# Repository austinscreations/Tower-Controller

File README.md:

# Tower Controller
# formerly mini-notification-tower

I've recently found good sellers for lower cost industrial towers, while I'll still 3d print my own 180 degree tower light and share files should someone want to build one, I've now designed a semi-universal controller for controlling analog 12-24v tower lights

New code can be found here: [Github](https://github.com/austinscreations/OXRS-AC-TowerController-ESP8266-FW) <br>
Load up a bin file in wifi or ethernet mode and provision the device using the admin UI: [Github](https://github.com/OXRS-IO/OXRS-IO-AdminUI-WEB-APP) <br>
Compatable with the (http://oxrs.io) system

As someone who has a home office and a workshop in the garage I wanted an easy way to have notifications whereever I am.
traditional 5 layer led notification lights are large and pricey.
I set out to make a smaller alternative solution. with 3d printing I made a 180 degree light, with the help of a 3d printed mold I was able to use epoxy resin and tints to create the lenses.

-

Red - flashing - immediate issue (such as a fire alarm or CO alarm)

Red - machine error (cnc or 3d printer)

Yellow - flashing - machine error / require attention (such as a 3d printer filament sensor or 3d print ends)

Yellow - equipement On - temperature related (3d printer active (hot end or heat bed) or soldering iron on)

Green - equipment on but idle (say 3d printer or soldering iron is on but not running a job

Blue - notifications (with the help of an I2C lcd I'm able to show messages

White - tied to my doorbell (one to my office door and front house door)

-

Version 1 used 5mm leds in a 3d printed insert - mosfets controlelr wired to 5v and arduino nano. the arduino nano was linked to an rf433 reciever for the doorbell.

Version 2 will include a PCB for a Wemos d1 mini and SMD leds, and I want to try to make a 360 degree model as well.
          
RF433 will be offloaded to a esp-01 to build a seprate gateway for my home assitant installation.

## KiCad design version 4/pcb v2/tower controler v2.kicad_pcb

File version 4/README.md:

this latest version include builtin ethernet support, POE support and runs on esp32

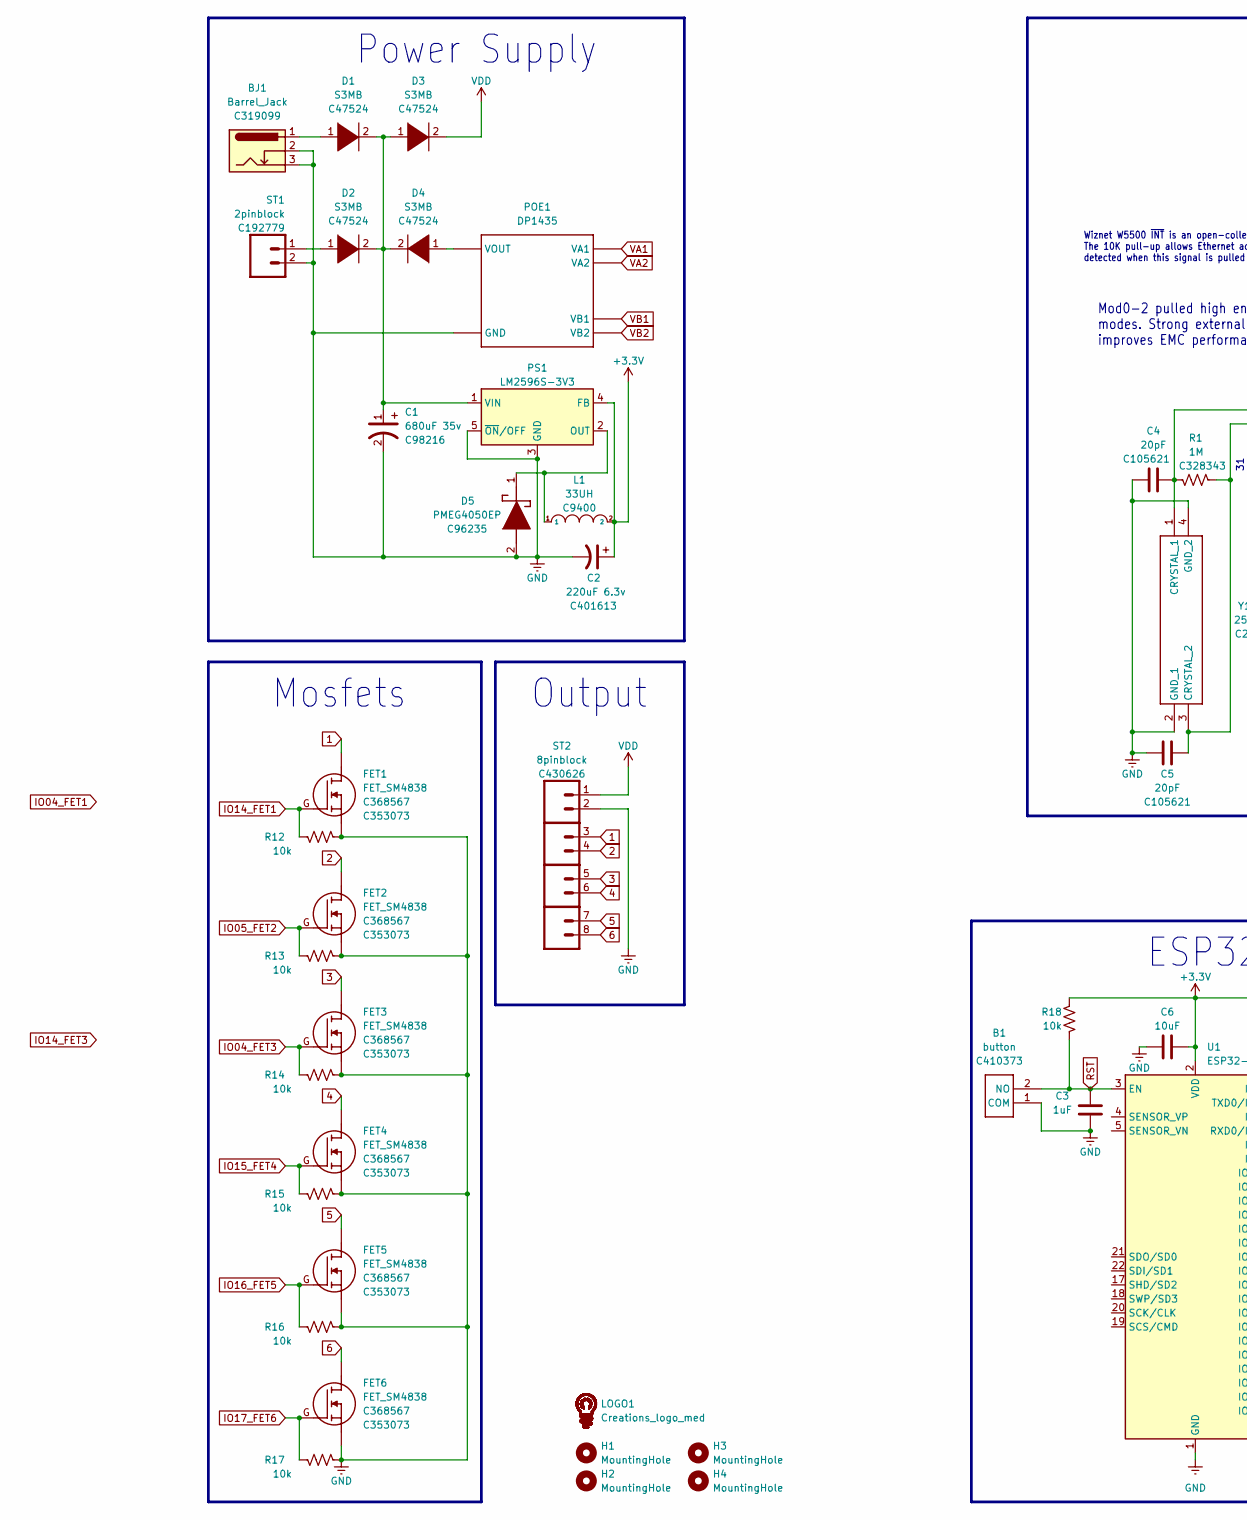
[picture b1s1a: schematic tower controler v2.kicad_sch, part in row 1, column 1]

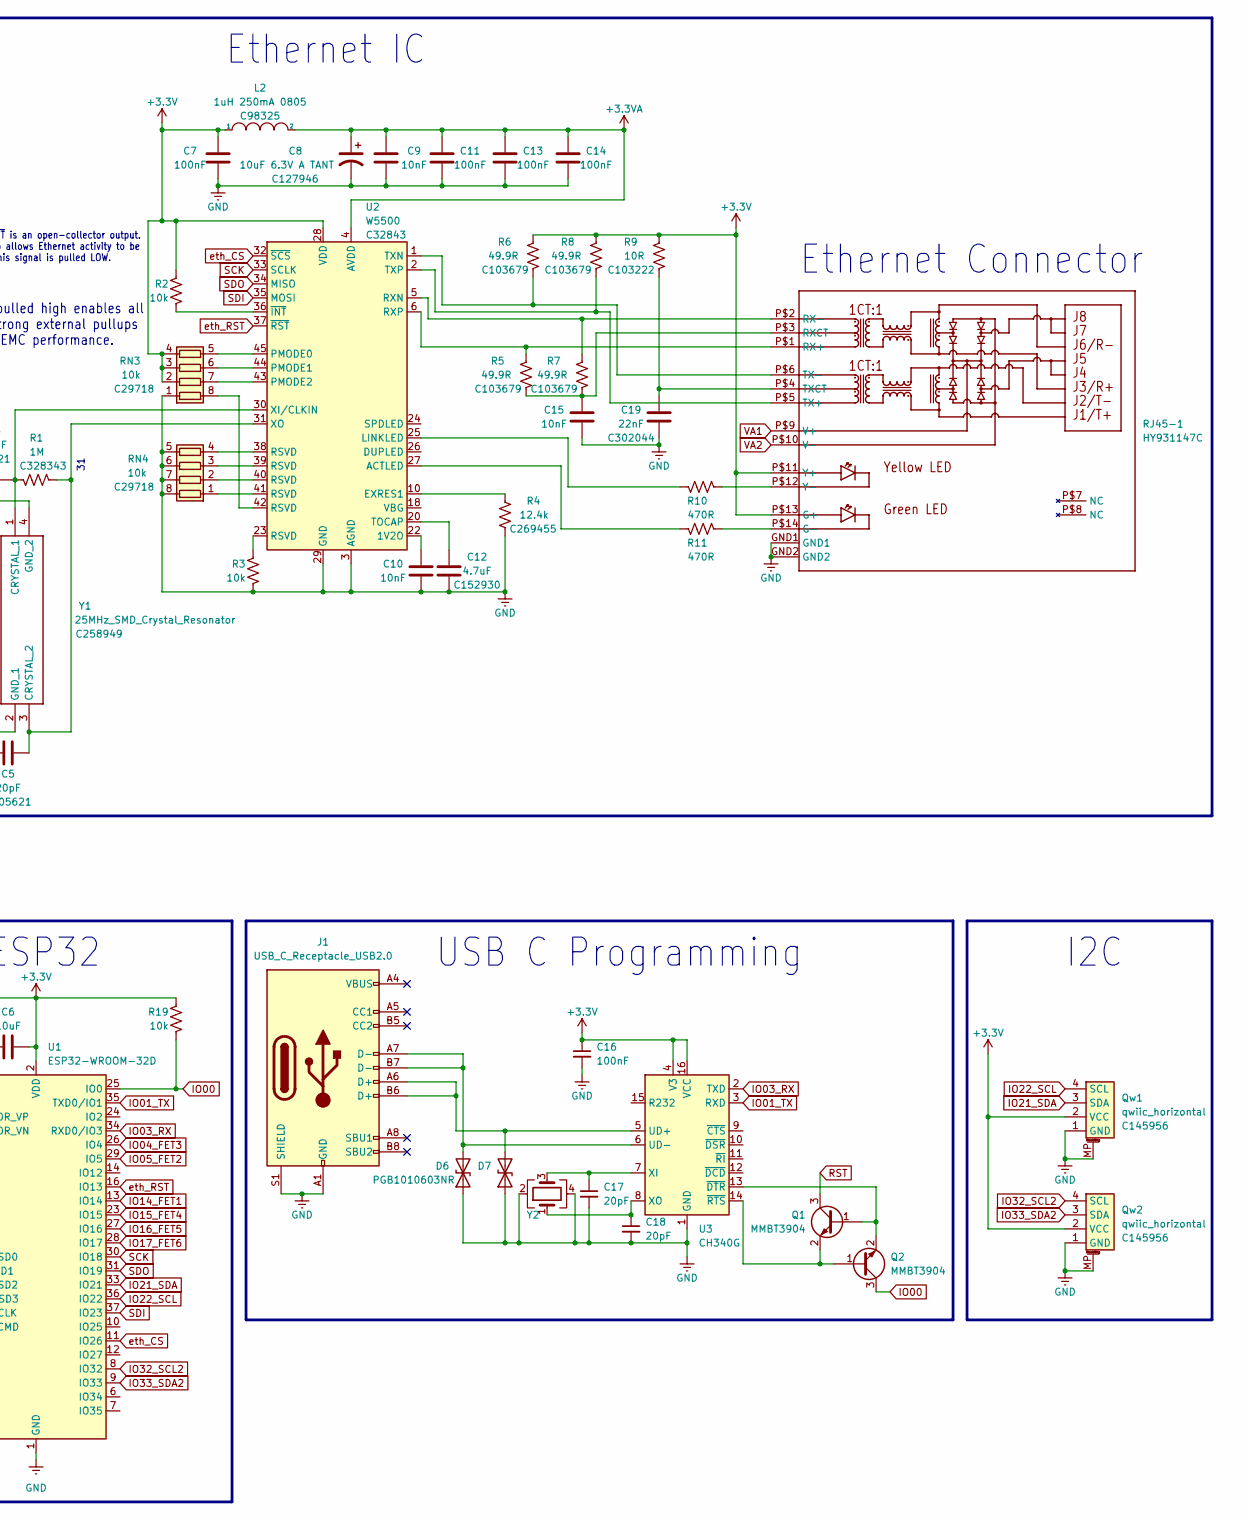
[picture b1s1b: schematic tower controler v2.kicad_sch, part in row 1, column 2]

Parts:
B1: button; part # C410373
BJ1: Barrel_Jack; Barrel Jack; part # C319099
C1: 680uF 35v; large capacitor 12.5d 13.5h; part # C98216
C2: 220uF 6.3v; CP_Elec_8x6.2; part # C401613
C3: 1uF; C_0603_1608Metric
C4, C5: 20pF; C_0603_1608Metric; part # C105621
C6: 10uF; C_0603_1608Metric
C7, C11, C13, C14, C16: 100nF; C_0603_1608Metric
C8: 10uF 6.3V A TANT; CP_EIA-3216-18_Kemet-A; part # C127946
C9, C10, C15: 10nF; C_0603_1608Metric
C12: 4.7uF; C_0603_1608Metric; part # C152930
C17, C18: 20pF; C_0603_1608Metric
C19: 22nF; C_0603_1608Metric; part # C302044
D1, D2, D3, D4: S3MB; D_SMB; part # C47524
D5: PMEG4050EP; PMEG3050EP; part # C96235
D6, D7: PGB1010603NR; D_0603_1608Metric
FET1, FET2, FET3, FET4, FET5, FET6: FET_SM4838; FET SM4838; part # C368567
H1, H2, H3, H4: MountingHole; MountingHole_3.2mm_M3
J1: USB_C_Receptacle_USB2.0; USB_C_Receptacle_HRO_TYPE-C-31-M-12
L1: 33UH; 12x12x8 inductor; part # C9400
L2: 1uH 250mA 0805; L_0805_2012Metric; part # C98325
LOGO1: Creations_logo_med; Creations logo med
POE1: DP1435
PS1: LM2596S-3V3; LM2596S
Q1, Q2: MMBT3904; SOT-23
Qw1, Qw2: qwiic_horizontal; qwiic horizontal; part # C145956
R1: 1M; R_0603_1608Metric; part # C328343
R2, R3, R12, R13, R14, R15, R16, R17, R18, R19: 10k; R_0603_1608Metric
R4: 12.4k; R_0603_1608Metric; part # C269455
R5, R6, R7, R8: 49.9R; R_0603_1608Metric; part # C103679
R9: 10R; R_0603_1608Metric; part # C103222
R10, R11: 470R; R_0603_1608Metric
RJ45-1: HY931147C
RN3, RN4: 10k; R_Array_Convex_4x0603; part # C29718
ST1: 2pinblock; part # C192779
ST2: 8pinblock; part # C430626
U1: ESP32-WROOM-32D; ESP32-WROOM-32
U2: W5500; LQFP-48_7x7mm_P0.5mm; part # C32843
U3: CH340G; SOIC-16_3.9x9.9mm_P1.27mm
Y1: 25MHz_SMD_Crystal_Resonator; part # C258949
Y2: Crystal_GND23; Crystal_SMD_3225-4Pin_3.2x2.5mm

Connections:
1: FET1.D, ST2.3
2: FET2.D, ST2.4
3: FET3.D, ST2.5
4: FET4.D, ST2.6
5: FET5.D, ST2.7
6: FET6.D, ST2.8
+3.3VA: C8.1, C9.2, C11.2, C13.2, C14.2, L2.2, U2.4 (AVDD), U2.8 (AVDD), U2.11 (AVDD), U2.15 (AVDD), U2.17 (AVDD), U2.21 (AVDD)
+3V3: C2.1, C6.2, C7.2, C16.1, L1.2, L2.1, PS1.4 (FB), Qw1.2 (VCC), Qw2.2 (VCC), R2.2, R6.2, R8.2, R9.2, R18.2, R19.2, RJ45-1.P$11 (Y+), RJ45-1.P$13 (G+), RN3.2 (R2.1), RN3.3 (R3.1), RN3.4 (R4.1), U1.2 (VDD), U2.28 (VDD), U3.4 (V3), U3.16 (VCC)
GNDREF: B1.1 (COM), BJ1.2, BJ1.3, C1.2, C2.2, C3.1, C4.1, C5.1, C6.1, C7.1, C8.2, C9.1, C10.1, C11.1, C12.1, C13.1, C14.1, C15.1, C16.2, C17.2, C18.2, C19.1, D5.2 (A), D6.1 (A1), D7.1 (A1), FET1.S, FET2.S, FET3.S, FET4.S, FET5.S, FET6.S, J1.A1 (GND), J1.A12 (GND), J1.B1 (GND), J1.B12 (GND), J1.S1 (SHIELD), POE1.GND, PS1.3 (GND), PS1.5 (~ON/OFF), Qw1.1 (GND), Qw1.MP, Qw2.1 (GND), Qw2.MP, R3.1, R4.1, R12.1, R13.1, R14.1, R15.1, R16.1, R17.1, RJ45-1.GND1, RJ45-1.GND2, RN3.1 (R1.1), RN4.5 (R4.2), RN4.6 (R3.2), RN4.7 (R2.2), RN4.8 (R1.2), ST1.2, ST2.2, U1.1 (GND), U1.15 (GND), U1.38 (GND), U1.39 (GND), U2.3 (AGND), U2.9 (AGND), U2.14 (AGND), U2.16 (AGND), U2.19 (AGND), U2.29 (GND), U2.48 (AGND), U3.1 (GND), Y1.2 (GND_1), Y1.4 (GND_2), Y2.2, Y2.4
IO00: Q2.3 (C), R19.1, U1.25 (IO0)
IO01_TX: U1.35 (TXD0/IO1), U3.3 (RXD)
IO03_RX: U1.34 (RXD0/IO3), U3.2 (TXD)
IO04_FET3: FET3.G, R14.2, U1.26 (IO4)
IO05_FET2: FET2.G, R13.2, U1.29 (IO5)
IO14_FET1: FET1.G, R12.2, U1.13 (IO14)
IO15_FET4: FET4.G, R15.2, U1.23 (IO15)
IO16_FET5: FET5.G, R16.2, U1.27 (IO16)
IO17_FET6: FET6.G, R17.2, U1.28 (IO17)
IO21_SDA: Qw1.3 (SDA), U1.33 (IO21)
IO22_SCL: Qw1.4 (SCL), U1.36 (IO22)
IO32_SCL2: Qw2.4 (SCL), U1.8 (IO32)
IO33_SDA2: Qw2.3 (SDA), U1.9 (IO33)
unnamed: BJ1.1, D1.1 (K)
unnamed: C1.1, D1.2 (A), D2.2 (A), D3.1 (K), D4.2 (A), PS1.1 (VIN)
unnamed: C4.2, R1.1, U2.30 (XI/CLKIN), Y1.1 (CRYSTAL_1)
unnamed: C5.2, R1.2, U2.31 (XO), Y1.3 (CRYSTAL_2)
unnamed: C10.2, U2.22 (1V2O)
unnamed: C12.2, U2.20 (TOCAP)
unnamed: C15.2, R5.1, R7.1, RJ45-1.P$3 (RXCT)
unnamed: C17.1, U3.7 (XI), Y2.3
unnamed: C18.1, U3.8 (XO), Y2.1
unnamed: C19.2, R9.1, RJ45-1.P$4 (TXCT)
unnamed: D2.1 (K), ST1.1
unnamed: D4.1 (K), POE1.VOUT
unnamed: D5.1 (K), L1.1, PS1.2 (OUT)
unnamed: D6.2 (A2), J1.A7 (D-), J1.B7 (D-), U3.6 (UD-)
unnamed: D7.2 (A2), J1.A6 (D+), J1.B6 (D+), U3.5 (UD+)
unnamed: Q1.1 (B), Q2.2 (E), U3.13 (~DTR)
unnamed: Q1.2 (E), Q2.1 (B), U3.14 (~RTS)
unnamed: R2.1, U2.36 (~INT)
unnamed: R3.2, U2.23 (RSVD)
unnamed: R4.2, U2.10 (EXRES1)
unnamed: R5.2, RJ45-1.P$1 (RX+), U2.6 (RXP)
unnamed: R6.1, RJ45-1.P$6 (TX-), U2.1 (TXN)
unnamed: R7.2, RJ45-1.P$2 (RX-), U2.5 (RXN)
unnamed: R8.1, RJ45-1.P$5 (TX+), U2.2 (TXP)
unnamed: R10.1, RJ45-1.P$12 (Y-)
unnamed: R10.2, U2.25 (LINKLED)
unnamed: R11.1, RJ45-1.P$14 (G-)
unnamed: R11.2, U2.27 (ACTLED)
unnamed: RN3.5 (R4.2), U2.45 (PMODE0)
unnamed: RN3.6 (R3.2), U2.44 (PMODE1)
unnamed: RN3.7 (R2.2), U2.43 (PMODE2)
unnamed: RN3.8 (R1.2), U2.42 (RSVD)
unnamed: RN4.1 (R1.1), U2.41 (RSVD)
unnamed: RN4.2 (R2.1), U2.40 (RSVD)
unnamed: RN4.3 (R3.1), U2.39 (RSVD)
unnamed: RN4.4 (R4.1), U2.38 (RSVD)
RST: B1.2 (NO), C3.2, Q1.3 (C), R18.1, U1.3 (EN)
SCK: U1.30 (IO18), U2.33 (SCLK)
SDI: U1.37 (IO23), U2.35 (MOSI)
SDO: U1.31 (IO19), U2.34 (MISO)
VA1: POE1.VA1, RJ45-1.P$9 (V+)
VA2: POE1.VA2, RJ45-1.P$10 (V-)
VB1: POE1.VB1
VB2: POE1.VB2
VDD: D3.2 (A), ST2.1
eth_CS: U1.11 (IO26), U2.32 (~SCS)
eth_RST: U1.16 (IO13), U2.37 (~RST)

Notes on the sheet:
Ethernet Connector
Ethernet IC
USB C Programming
ESP32
Power Supply
Mod0-2 pulled high enables all modes. Strong external pullups improves EMC performance.
Output
Mosfets
I2C
Wiznet W5500 ~{INT} is an open-collector output. The 10K pull-up allows Ethernet activity to be detected when this signal is pulled LOW.

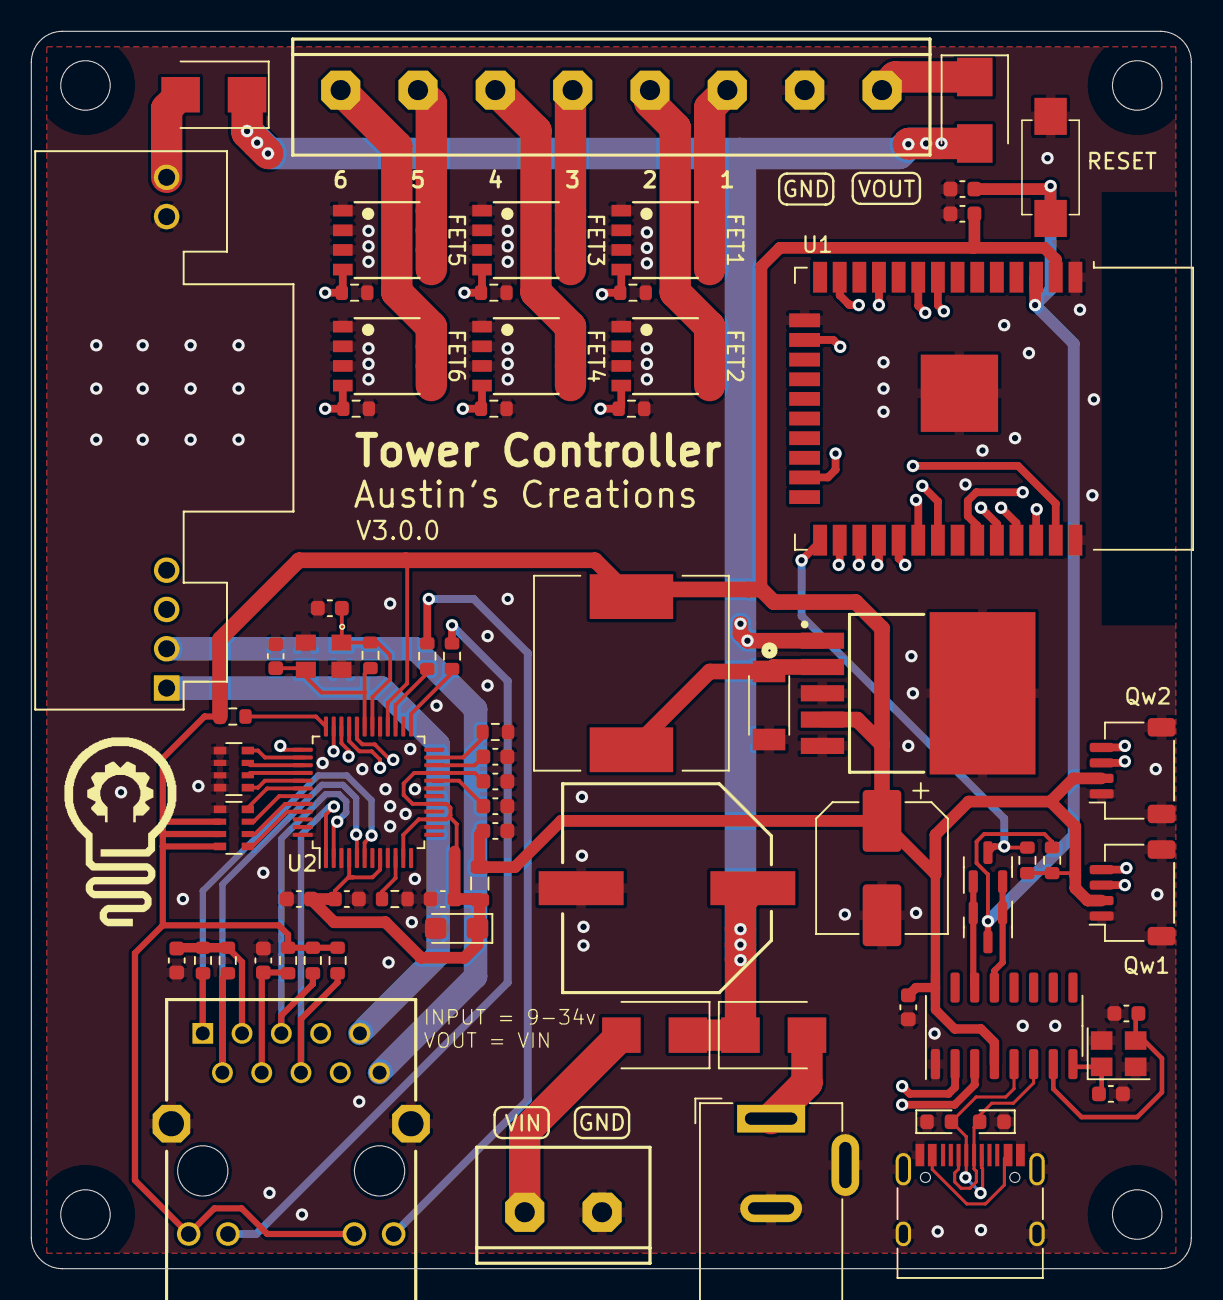
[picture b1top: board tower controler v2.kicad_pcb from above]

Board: 4 copper layers, 75.0 x 80.0 mm, 77 parts (0 on the bottom side), 67 nets.

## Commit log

2022-01-15 remove repeated chunk of code
2022-01-26 new oxrs code + readme
2022-01-26 spelling
2022-02-02 new version to match changes to OXRS_SENSORS library
2022-02-05 bh1750 library changed
2022-02-05 fitment clearance around ethernet jack
2022-02-06 updating height to better fit sensors
2022-02-09 wrong values for OLED control fixed
2022-05-04 code is obsolete
2022-05-04 updating spelling and new code link
2022-12-27 add latest version
